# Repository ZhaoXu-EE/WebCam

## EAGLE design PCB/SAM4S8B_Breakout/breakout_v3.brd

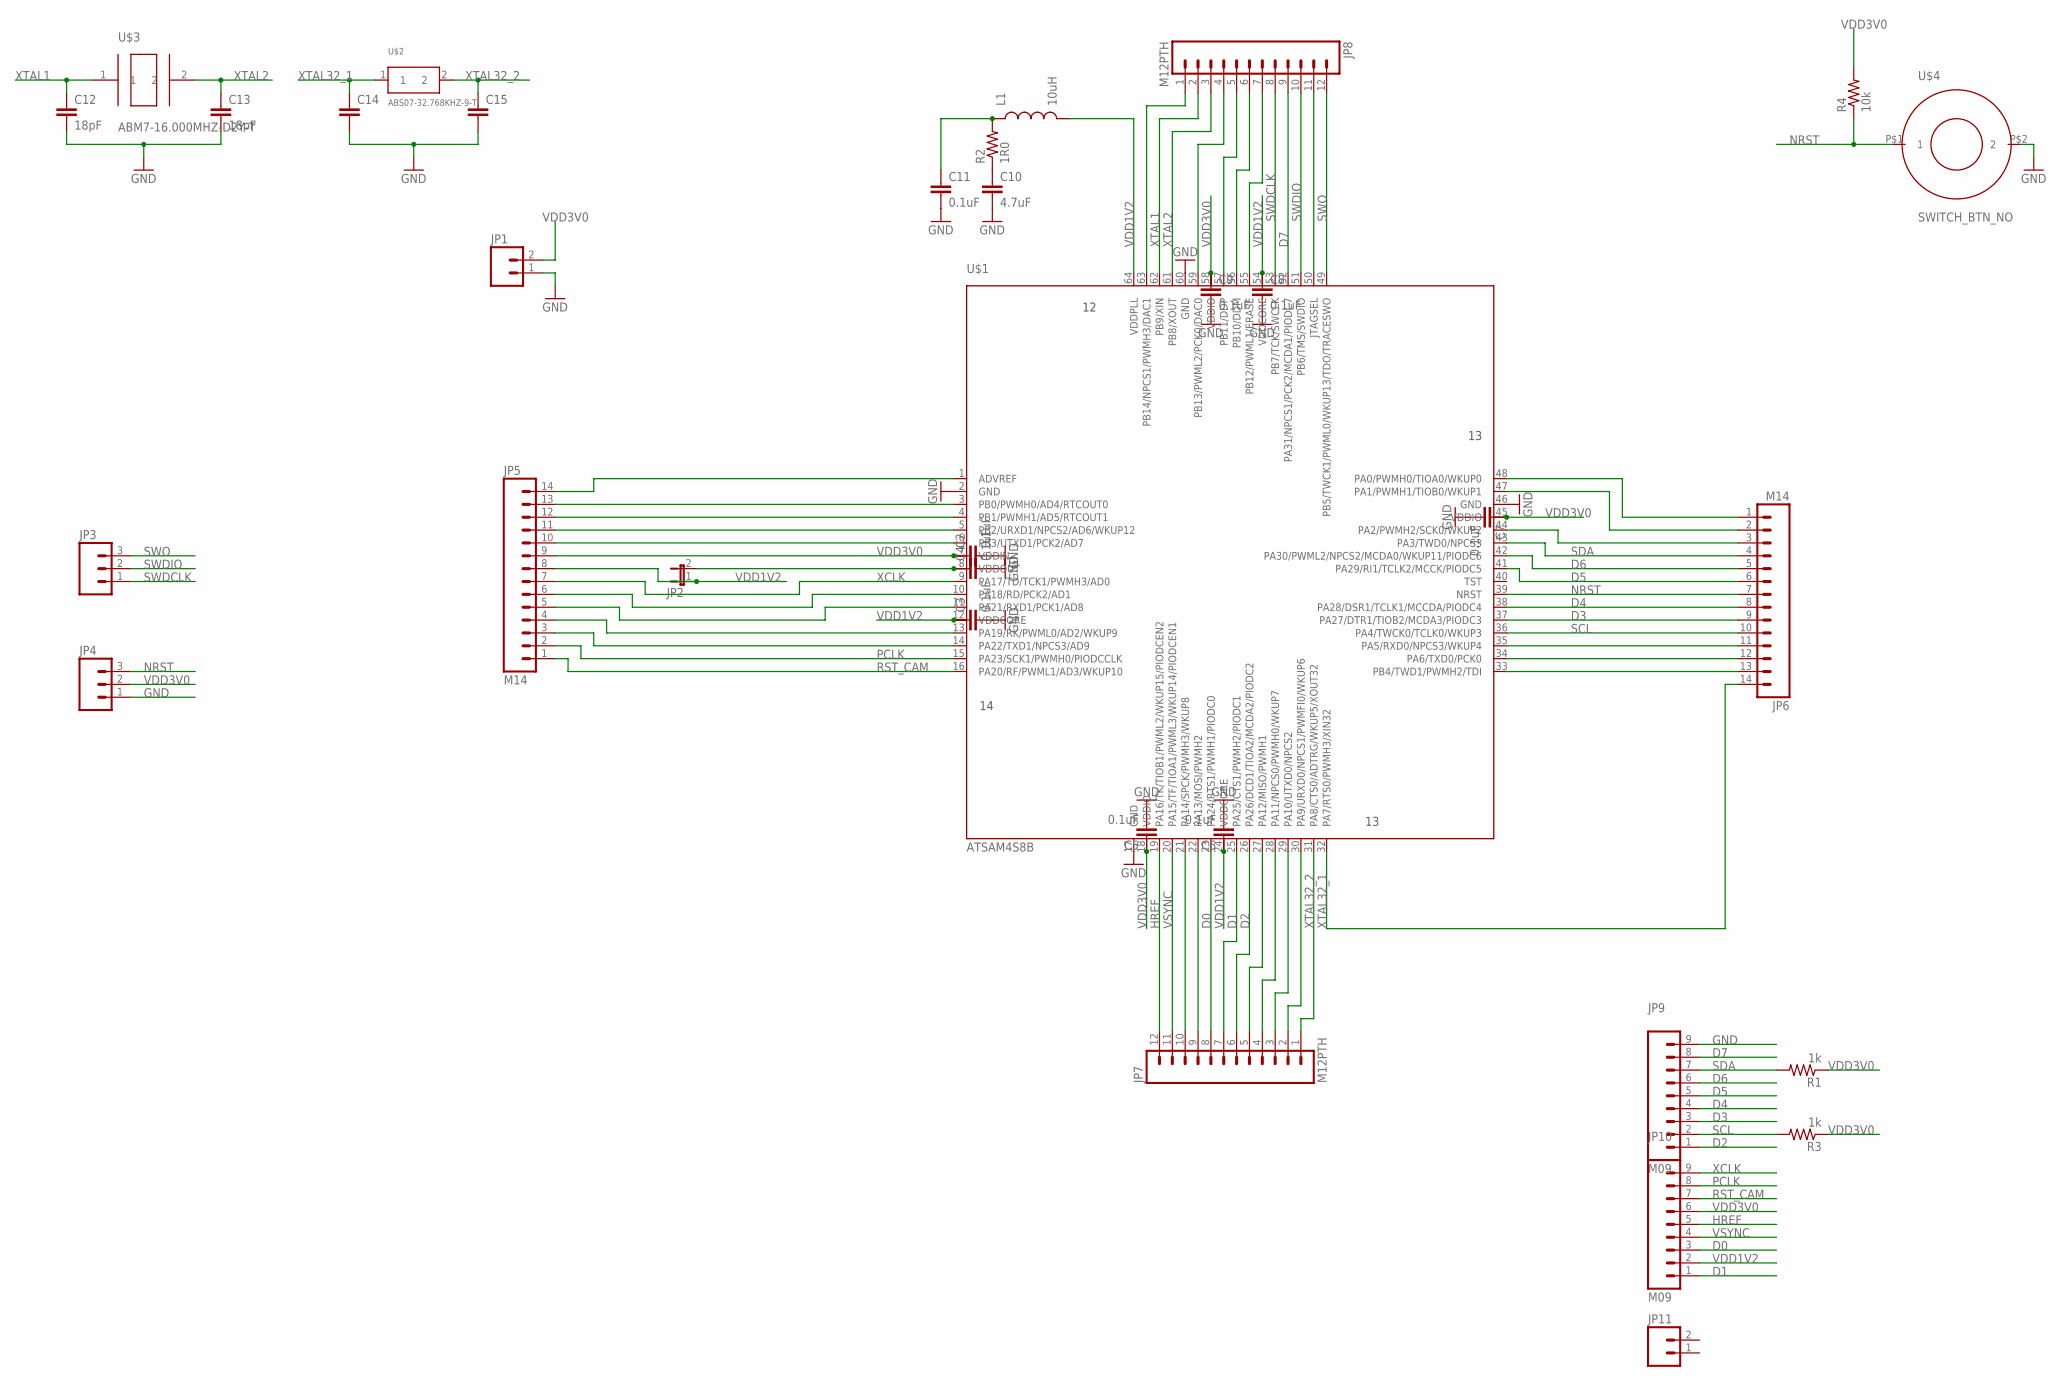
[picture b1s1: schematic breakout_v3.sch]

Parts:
C2, C3, C4, C5, C6, C7, C8, C9, C11: 0.1uF; 0805
C10: 4.7uF; 0805
C12, C13: 18pF; 0805
C14, C15: CAP0805; 0805
JP1, JP11: M02PTH; 1X02
JP2: JUMPER-2PTH; 1X02
JP3, JP4: M03PTH; 1X03
JP5, JP6: M14; 1X14
JP7, JP8: M12PTH; 1X12
JP9, JP10: M09; 1X09
L1: 10uH; 0805
R1, R3: 1k; 0805
R2: 1R0; 0805
R4: 10k; 0805
U$1: ATSAM4S8B; QFP50P1200X1200X160-64N
U$2: ABS07-32.768KHZ-9-T
U$3: ABM7-16.000MHZ-D2Y-T
U$4: SWITCH_BTN_NO; BTN_2

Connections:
D0: JP7.8, JP10.3, U$1.23 (PA24/RTS1/PWMH1/PIODC0)
D1: JP7.7, JP10.1, U$1.25 (PA25/CTS1/PWMH2/PIODC1)
D2: JP7.6, JP9.1, U$1.26 (PA26/DCD1/TIOA2/MCDA2/PIODC2)
D3: JP6.9, JP9.3, U$1.37 (PA27/DTR1/TIOB2/MCDA3/PIODC3)
D4: JP6.8, JP9.4, U$1.38 (PA28/DSR1/TCLK1/MCCDA/PIODC4)
D5: JP6.6, JP9.5, U$1.41 (PA29/RI1/TCLK2/MCCK/PIODC5)
D6: JP6.5, JP9.6, U$1.42 (PA30/PWML2/NPCS2/MCDA0/WKUP11/PIODC6)
D7: JP8.9, JP9.8, U$1.52 (PA31/NPCS1/PCK2/MCDA1/PIODC7)
GND: C2.2, C3.2, C4.2, C5.2, C6.2, C7.2, C8.2, C9.2, C10.2, C11.2, C12.2, C13.2, C14.2, C15.2, JP1.1, JP4.1, JP9.9, U$1.2 (GND), U$1.17 (GND), U$1.46 (GND), U$1.60 (GND), U$4.P$2 (2)
HREF: JP7.12, JP10.5, U$1.19 (PA16/TK/TIOB1/PWML2/WKUP15/PIODCEN2)
unnamed: C4.1, JP2.2, U$1.8 (VDDOUT)
unnamed: C11.1, L1.1, R2.2
unnamed: C10.1, R2.1
unnamed: JP5.14, U$1.1 (ADVREF)
unnamed: JP5.13, U$1.3 (PB0/PWMH0/AD4/RTCOUT0)
unnamed: JP5.12, U$1.4 (PB1/PWMH1/AD5/RTCOUT1)
unnamed: JP5.11, U$1.5 (PB2/URXD1/NPCS2/AD6/WKUP12)
unnamed: JP5.10, U$1.6 (PB3/UTXD1/PCK2/AD7)
unnamed: JP5.6, U$1.10 (PA18/RD/PCK2/AD1)
unnamed: JP5.5, U$1.11 (PA21/RXD1/PCK1/AD8)
unnamed: JP5.4, U$1.13 (PA19/RK/PWML0/AD2/WKUP9)
unnamed: JP5.3, U$1.14 (PA22/TXD1/NPCS3/AD9)
unnamed: JP7.10, U$1.21 (PA14/SPCK/PWMH3/WKUP8)
unnamed: JP7.9, U$1.22 (PA13/MOSI/PWMH2)
unnamed: JP7.5, U$1.27 (PA12/MISO/PWMH1)
unnamed: JP7.4, U$1.28 (PA11/NPCS0/PWMH0/WKUP7)
unnamed: JP7.3, U$1.29 (PA10/UTXD0/NPCS2)
unnamed: JP7.2, U$1.30 (PA9/URXD0/NPCS1/PWMFI0/WKUP6)
unnamed: JP6.13, U$1.33 (PB4/TWD1/PWMH2/TDI)
unnamed: JP6.12, U$1.34 (PA6/TXD0/PCK0)
unnamed: JP6.11, U$1.35 (PA5/RXD0/NPCS3/WKUP4)
unnamed: JP6.3, U$1.44 (PA2/PWMH2/SCK0/WKUP2)
unnamed: JP6.2, U$1.47 (PA1/PWMH1/TIOB0/WKUP1)
unnamed: JP6.1, U$1.48 (PA0/PWMH0/TIOA0/WKUP0)
unnamed: JP8.11, U$1.50 (JTAGSEL)
unnamed: JP8.7, U$1.55 (PB12/PWML1/ERASE)
unnamed: JP8.6, U$1.56 (PB10/DDM)
unnamed: JP8.5, U$1.57 (PB11/DDP)
unnamed: JP8.4, U$1.59 (PB13/PWML2/PCK0/DAC0)
unnamed: JP8.1, U$1.63 (PB14/NPCS1/PWMH3/DAC1)
NRST: JP4.3, JP6.7, R4.1, U$1.39 (NRST), U$4.P$1 (1)
PCLK: JP5.2, JP10.8, U$1.15 (PA23/SCK1/PWMH0/PIODCCLK)
RST_CAM: JP5.1, JP10.7, U$1.16 (PA20/RF/PWML1/AD3/WKUP10)
SCL: JP6.10, JP9.2, R3.2, U$1.36 (PA4/TWCK0/TCLK0/WKUP3)
SDA: JP6.4, JP9.7, R1.2, U$1.43 (PA3/TWD0/NPCS3)
SWDCLK: JP3.1, JP8.8, U$1.53 (PB7/TCK/SWCLK)
SWDIO: JP3.2, JP8.10, U$1.51 (PB6/TMS/SWDIO)
SWO: JP3.3, JP8.12, U$1.49 (PB5/TWCK1/PWML0/WKUP13/TDO/TRACESWO)
VDD1V2: C3.1, C6.1, C8.1, JP2.1, JP5.8, JP10.2, L1.2, U$1.12 (VDDCORE), U$1.24 (VDDCORE), U$1.54 (VDDCORE), U$1.64 (VDDPLL)
VDD3V0: C2.1, C5.1, C7.1, C9.1, JP1.2, JP4.2, JP5.9, JP10.6, R1.1, R3.1, R4.2, U$1.7 (VDDIN), U$1.18 (VDDIO), U$1.45 (VDDIO), U$1.58 (VDDIO)
VSYNC: JP7.11, JP10.4, U$1.20 (PA15/TF/TIOA1/PWML3/WKUP14/PIODCEN1)
XCLK: JP5.7, JP10.9, U$1.9 (PA17/TD/TCK1/PWMH3/AD0)
XTAL1: C12.1, JP8.2, U$1.62 (PB9/XIN), U$3.1
XTAL2: C13.1, JP8.3, U$1.61 (PB8/XOUT), U$3.2
XTAL32_1: C14.1, JP6.14, U$1.32 (PA7/RTS0/PWMH3/XIN32), U$2.1
XTAL32_2: C15.1, JP7.1, U$1.31 (PA8/CTS0/ADTRG/WKUP5/XOUT32), U$2.2

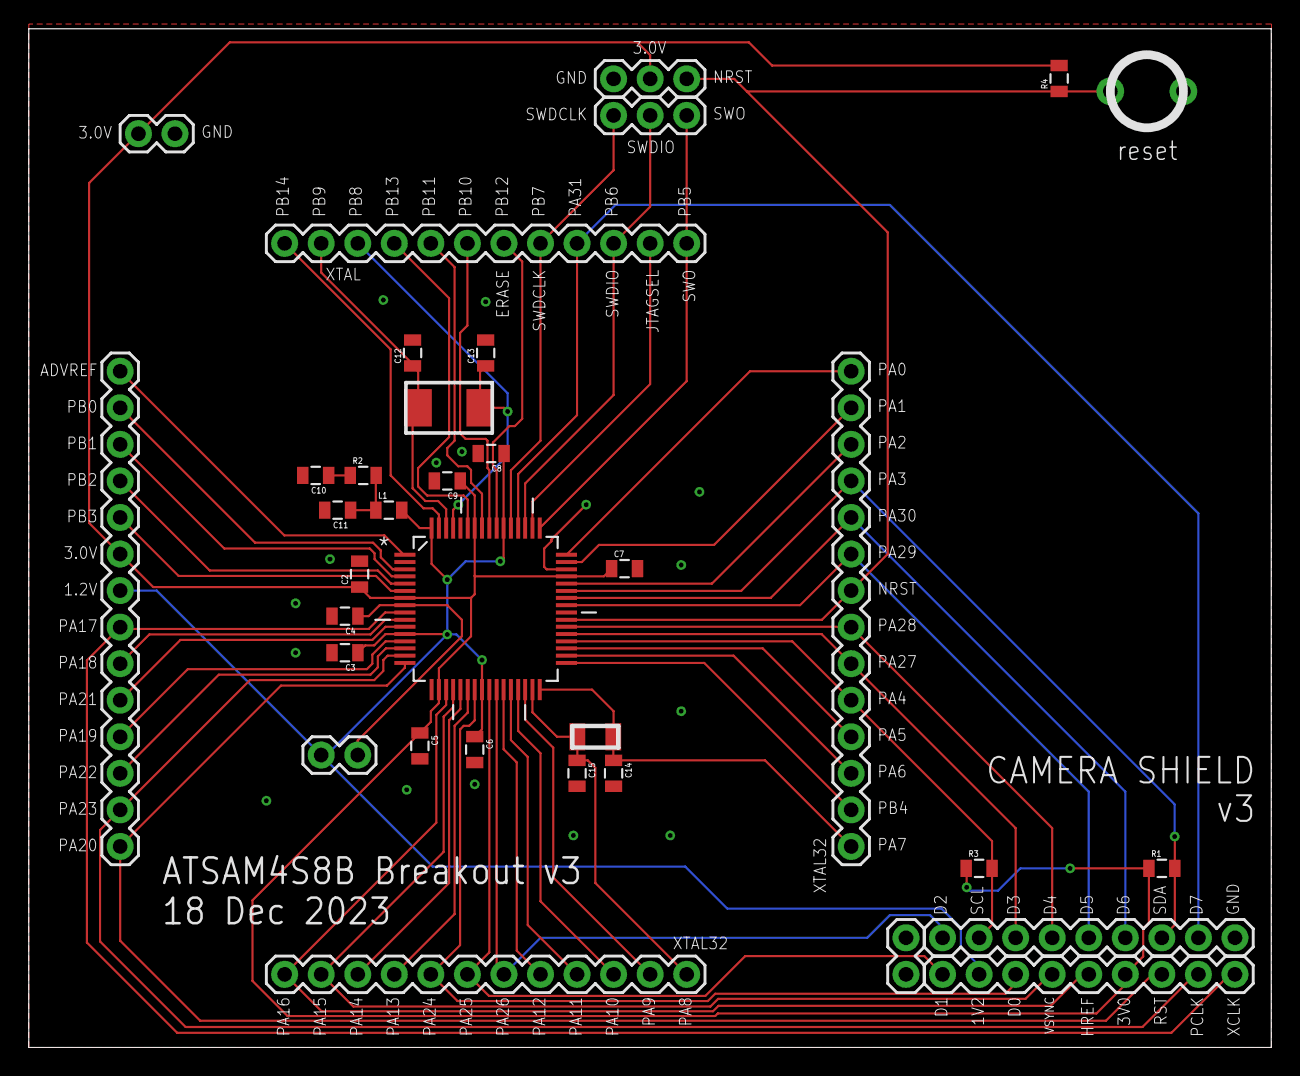
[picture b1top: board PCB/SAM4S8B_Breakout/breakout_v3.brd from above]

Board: 2 copper layers, 86.3 x 70.8 mm, 34 parts (0 on the bottom side), 56 nets.

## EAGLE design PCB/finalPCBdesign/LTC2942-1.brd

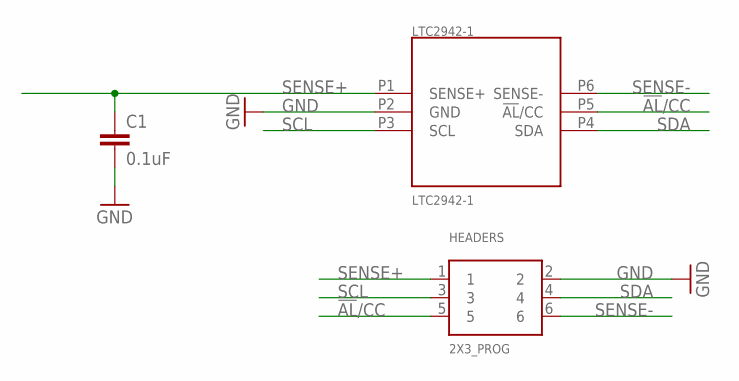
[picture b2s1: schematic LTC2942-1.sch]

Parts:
C1: 0.1uF; 0805
HEADERS: 2X3_PROG; 2X3_0.1IN
LTC2942-1: LTC2942-1

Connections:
!AL!/CC: HEADERS.5, LTC2942-1.P5 (!AL!/CC)
GND: C1.2, HEADERS.2, LTC2942-1.P2 (GND)
SCL: HEADERS.3, LTC2942-1.P3 (SCL)
SDA: HEADERS.4, LTC2942-1.P4 (SDA)
SENSE+: C1.1, HEADERS.1, LTC2942-1.P1 (SENSE+)
SENSE-: HEADERS.6, LTC2942-1.P6 (SENSE-)

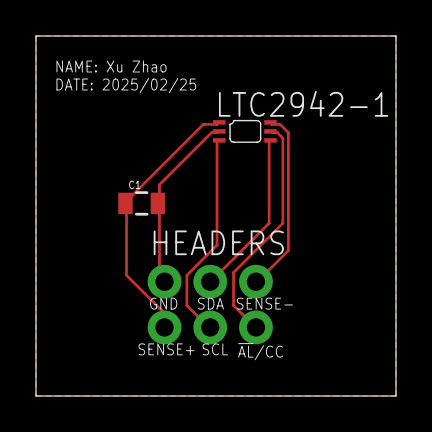
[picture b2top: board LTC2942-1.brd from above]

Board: 2 copper layers, 20.0 x 20.0 mm, 3 parts (0 on the bottom side), 6 nets.

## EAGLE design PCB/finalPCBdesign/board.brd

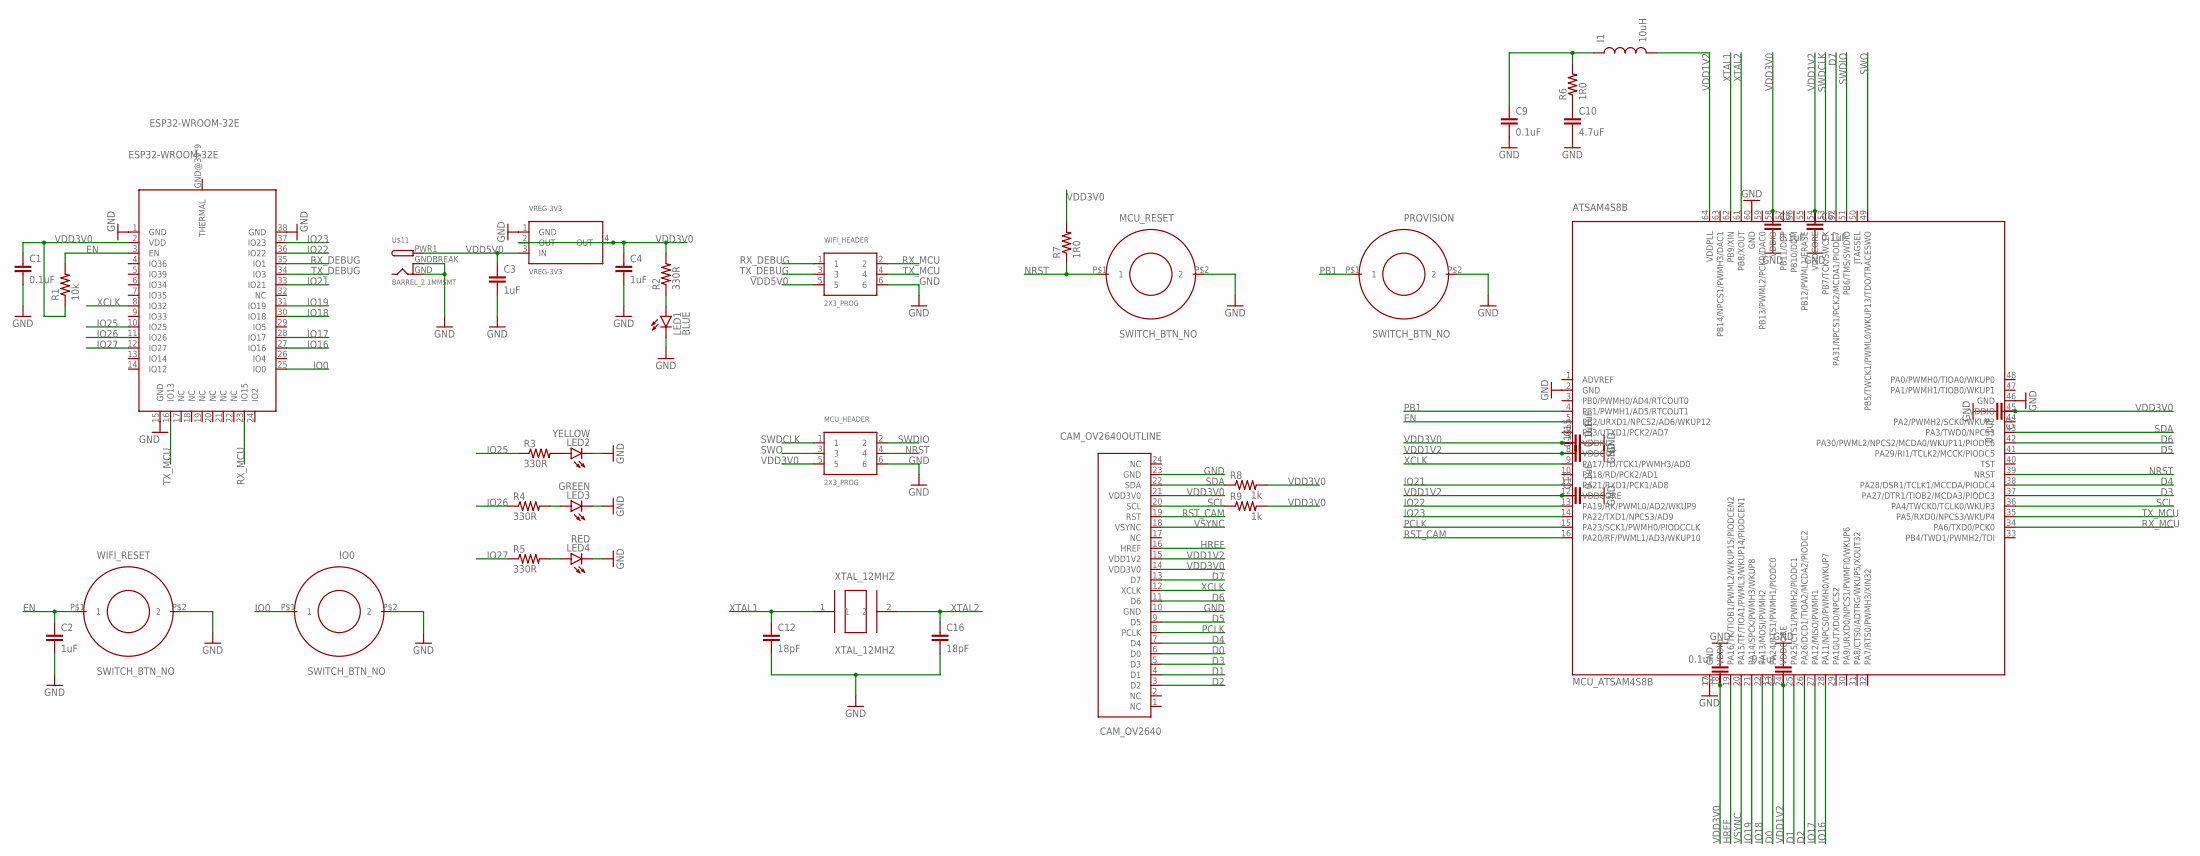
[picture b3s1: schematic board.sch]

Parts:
ATSAM4S8B: MCU_ATSAM4S8B; QFP50P1200X1200X160-64N
C1, C5, C6, C7, C8, C9, C11, C13, C14, C15: 0.1uF; 0805
C2, C3, C4: 1uF; 0805
C10: 4.7uF; 0805
C12, C16: 18pF; 0805
CAM_OV2640: CAM_OV2640OUTLINE; CAM_CONN
ESP32-WROOM-32E: ESP32-WROOM-32E
I1: 10uH; 0805
IO0: SWITCH_BTN_NO; BTN_2
LED1: BLUE; LED-0603
LED2: YELLOW; LED-0603
LED3: GREEN; LED-0603
LED4: RED; LED-0603
MCU_HEADER: 2X3_PROG; 2X3_0.1IN
MCU_RESET: SWITCH_BTN_NO; BTN_2
PROVISION: SWITCH_BTN_NO; BTN_2
R1: 10k; 0805
R2, R3, R4, R5: 330R; 0805
R6, R7: 1R0; 0805
R8, R9: 1k; 0805
U$11: BARREL_2.1MMSMT; DCJACK_2MM_SMT
VREG-3V3: VREG-3V3; R-PDSO-G4_TI
WIFI_HEADER: 2X3_PROG; 2X3_0.1IN
WIFI_RESET: SWITCH_BTN_NO; BTN_2
XTAL_12MHZ: XTAL_12MHZ; ABM7-16.000MHZ-D2Y-T

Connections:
D0: ATSAM4S8B.23 (PA24/RTS1/PWMH1/PIODC0), CAM_OV2640.6 (D0)
D1: ATSAM4S8B.25 (PA25/CTS1/PWMH2/PIODC1), CAM_OV2640.4 (D1)
D2: ATSAM4S8B.26 (PA26/DCD1/TIOA2/MCDA2/PIODC2), CAM_OV2640.3 (D2)
D3: ATSAM4S8B.37 (PA27/DTR1/TIOB2/MCDA3/PIODC3), CAM_OV2640.5 (D3)
D4: ATSAM4S8B.38 (PA28/DSR1/TCLK1/MCCDA/PIODC4), CAM_OV2640.7 (D4)
D5: ATSAM4S8B.41 (PA29/RI1/TCLK2/MCCK/PIODC5), CAM_OV2640.9 (D5)
D6: ATSAM4S8B.42 (PA30/PWML2/NPCS2/MCDA0/WKUP11/PIODC6), CAM_OV2640.11 (D6)
D7: ATSAM4S8B.52 (PA31/NPCS1/PCK2/MCDA1/PIODC7), CAM_OV2640.13 (D7)
EN: ATSAM4S8B.5 (PB2/URXD1/NPCS2/AD6/WKUP12), C2.1, ESP32-WROOM-32E.3 (EN), R1.2, WIFI_RESET.P$1 (1)
GND: ATSAM4S8B.2 (GND), ATSAM4S8B.17 (GND), ATSAM4S8B.46 (GND), ATSAM4S8B.60 (GND), C1.2, C2.2, C3.2, C4.2, C5.2, C6.2, C7.2, C8.2, C9.2, C10.2, C11.2, C12.2, C13.2, C14.2, C15.2, C16.2, CAM_OV2640.10 (GND), CAM_OV2640.23 (GND), ESP32-WROOM-32E.1 (GND), ESP32-WROOM-32E.15 (GND), ESP32-WROOM-32E.38 (GND), IO0.P$2 (2), LED1.C, LED2.C, LED3.C, LED4.C, MCU_HEADER.6, MCU_RESET.P$2 (2), PROVISION.P$2 (2), U$11.GND, U$11.GNDBREAK, VREG-3V3.1 (GND), WIFI_HEADER.6, WIFI_RESET.P$2 (2)
HREF: ATSAM4S8B.19 (PA16/TK/TIOB1/PWML2/WKUP15/PIODCEN2), CAM_OV2640.16 (HREF)
IO0: ESP32-WROOM-32E.25 (IO0), IO0.P$1 (1)
IO16: ATSAM4S8B.28 (PA11/NPCS0/PWMH0/WKUP7), ESP32-WROOM-32E.27 (IO16)
IO17: ATSAM4S8B.27 (PA12/MISO/PWMH1), ESP32-WROOM-32E.28 (IO17)
IO18: ATSAM4S8B.22 (PA13/MOSI/PWMH2), ESP32-WROOM-32E.30 (IO18)
IO19: ATSAM4S8B.21 (PA14/SPCK/PWMH3/WKUP8), ESP32-WROOM-32E.31 (IO19)
IO21: ATSAM4S8B.11 (PA21/RXD1/PCK1/AD8), ESP32-WROOM-32E.33 (IO21)
IO22: ATSAM4S8B.13 (PA19/RK/PWML0/AD2/WKUP9), ESP32-WROOM-32E.36 (IO22)
IO23: ATSAM4S8B.14 (PA22/TXD1/NPCS3/AD9), ESP32-WROOM-32E.37 (IO23)
IO25: ESP32-WROOM-32E.10 (IO25), R3.1
IO26: ESP32-WROOM-32E.11 (IO26), R4.1
IO27: ESP32-WROOM-32E.12 (IO27), R5.1
unnamed: LED1.A, R2.1
unnamed: LED2.A, R3.2
unnamed: LED3.A, R4.2
unnamed: LED4.A, R5.2
unnamed: C10.1, R6.1
unnamed: C9.1, I1.1, R6.2
NRST: ATSAM4S8B.39 (NRST), MCU_HEADER.4, MCU_RESET.P$1 (1), R7.1
PB1: ATSAM4S8B.4 (PB1/PWMH1/AD5/RTCOUT1), PROVISION.P$1 (1)
PCLK: ATSAM4S8B.15 (PA23/SCK1/PWMH0/PIODCCLK), CAM_OV2640.8 (PCLK)
RST_CAM: ATSAM4S8B.16 (PA20/RF/PWML1/AD3/WKUP10), CAM_OV2640.19 (RST)
RX_DEBUG: ESP32-WROOM-32E.35 (IO1), WIFI_HEADER.1
RX_MCU: ATSAM4S8B.34 (PA6/TXD0/PCK0), ESP32-WROOM-32E.23 (IO15), WIFI_HEADER.2
SCL: ATSAM4S8B.36 (PA4/TWCK0/TCLK0/WKUP3), CAM_OV2640.20 (SCL), R9.1
SDA: ATSAM4S8B.43 (PA3/TWD0/NPCS3), CAM_OV2640.22 (SDA), R8.1
SWDCLK: ATSAM4S8B.53 (PB7/TCK/SWCLK), MCU_HEADER.1
SWDIO: ATSAM4S8B.51 (PB6/TMS/SWDIO), MCU_HEADER.2
SWO: ATSAM4S8B.49 (PB5/TWCK1/PWML0/WKUP13/TDO/TRACESWO), MCU_HEADER.3
TX_DEBUG: ESP32-WROOM-32E.34 (IO3), WIFI_HEADER.3
TX_MCU: ATSAM4S8B.35 (PA5/RXD0/NPCS3/WKUP4), ESP32-WROOM-32E.16 (IO13), WIFI_HEADER.4
VDD1V2: ATSAM4S8B.8 (VDDOUT), ATSAM4S8B.12 (VDDCORE), ATSAM4S8B.24 (VDDCORE), ATSAM4S8B.54 (VDDCORE), ATSAM4S8B.64 (VDDPLL), C6.1, C11.1, C13.1, C14.1, CAM_OV2640.15 (VDD1V2), I1.2
VDD3V0: ATSAM4S8B.7 (VDDIN), ATSAM4S8B.18 (VDDIO), ATSAM4S8B.45 (VDDIO), ATSAM4S8B.58 (VDDIO), C1.1, C4.1, C5.1, C7.1, C8.1, C15.1, CAM_OV2640.14 (VDD3V0), CAM_OV2640.21 (VDD3V0), ESP32-WROOM-32E.2 (VDD), MCU_HEADER.5, R1.1, R2.2, R7.2, R8.2, R9.2, VREG-3V3.2 (OUT), VREG-3V3.4 (OUT)
VDD5V0: C3.1, U$11.PWR1 (PWR), VREG-3V3.3 (IN), WIFI_HEADER.5
VSYNC: ATSAM4S8B.20 (PA15/TF/TIOA1/PWML3/WKUP14/PIODCEN1), CAM_OV2640.18 (VSYNC)
XCLK: ATSAM4S8B.9 (PA17/TD/TCK1/PWMH3/AD0), CAM_OV2640.12 (XCLK), ESP32-WROOM-32E.8 (IO32)
XTAL1: ATSAM4S8B.62 (PB9/XIN), C12.1, XTAL_12MHZ.1
XTAL2: ATSAM4S8B.61 (PB8/XOUT), C16.1, XTAL_12MHZ.2

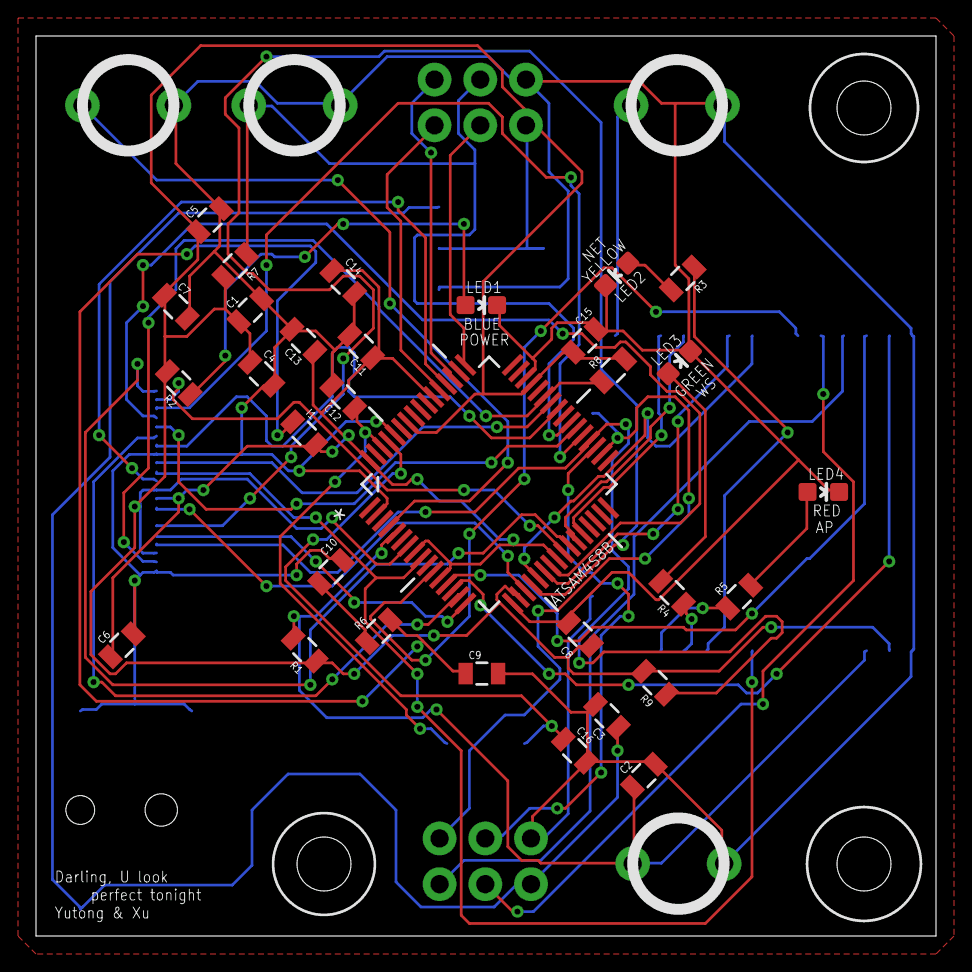
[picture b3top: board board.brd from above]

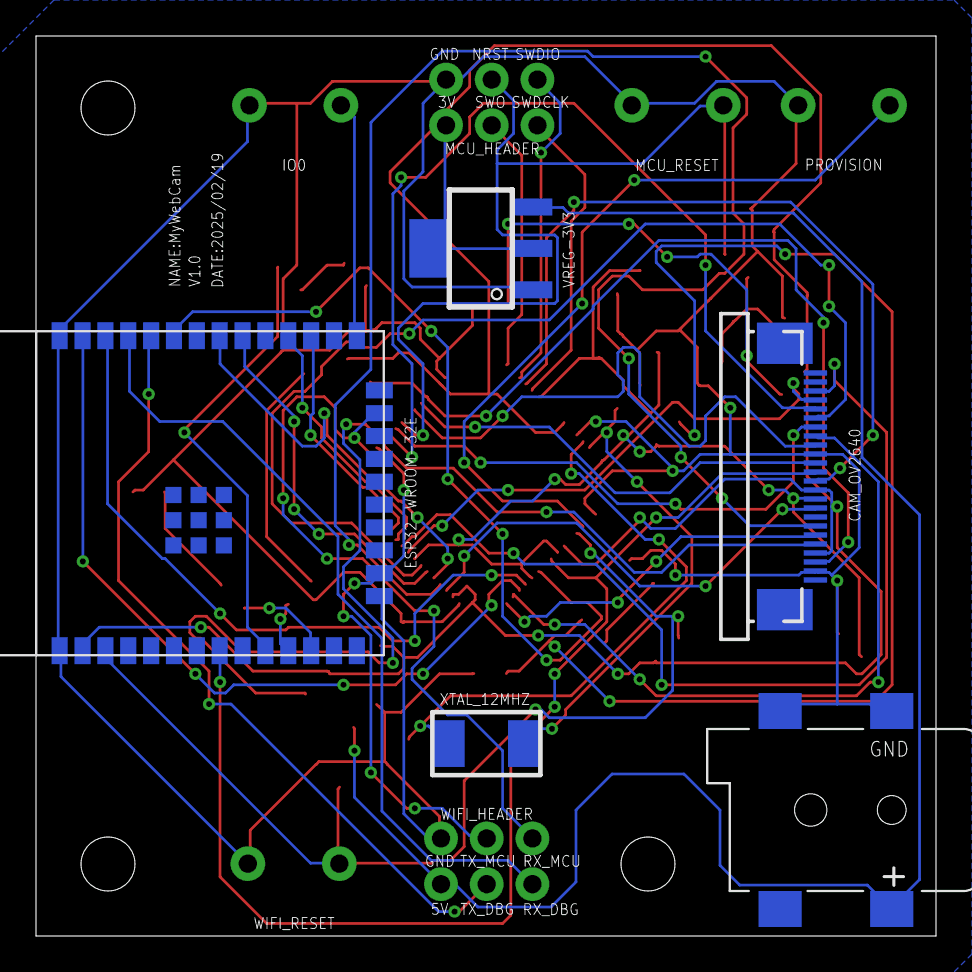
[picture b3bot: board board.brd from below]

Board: 2 copper layers, 50.0 x 50.0 mm, 42 parts (5 on the bottom side), 48 nets.

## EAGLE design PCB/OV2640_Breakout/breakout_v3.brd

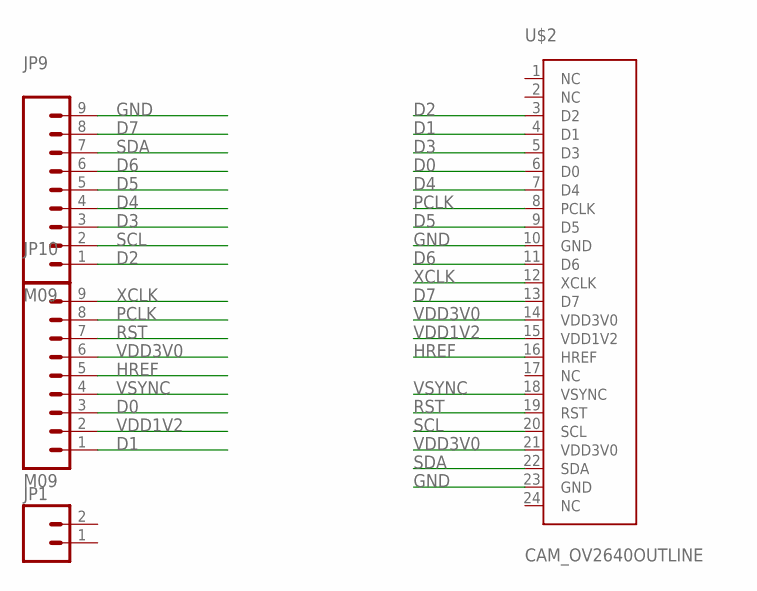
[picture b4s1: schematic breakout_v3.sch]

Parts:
JP1: M02PTH; 1X02
JP9, JP10: M09; 1X09
U$2: CAM_OV2640OUTLINE; CAM_CONN

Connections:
D0: JP10.3, U$2.6 (D0)
D1: JP10.1, U$2.4 (D1)
D2: JP9.1, U$2.3 (D2)
D3: JP9.3, U$2.5 (D3)
D4: JP9.4, U$2.7 (D4)
D5: JP9.5, U$2.9 (D5)
D6: JP9.6, U$2.11 (D6)
D7: JP9.8, U$2.13 (D7)
GND: JP9.9, U$2.10 (GND), U$2.23 (GND)
HREF: JP10.5, U$2.16 (HREF)
PCLK: JP10.8, U$2.8 (PCLK)
RST: JP10.7, U$2.19 (RST)
SCL: JP9.2, U$2.20 (SCL)
SDA: JP9.7, U$2.22 (SDA)
VDD1V2: JP10.2, U$2.15 (VDD1V2)
VDD3V0: JP10.6, U$2.14 (VDD3V0), U$2.21 (VDD3V0)
VSYNC: JP10.4, U$2.18 (VSYNC)
XCLK: JP10.9, U$2.12 (XCLK)

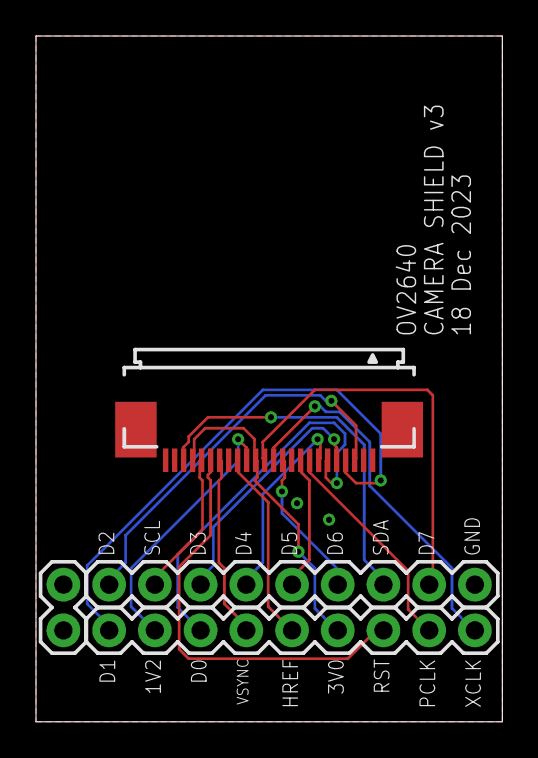
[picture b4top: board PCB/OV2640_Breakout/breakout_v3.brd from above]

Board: 2 copper layers, 25.9 x 38.1 mm, 4 parts (0 on the bottom side), 18 nets.

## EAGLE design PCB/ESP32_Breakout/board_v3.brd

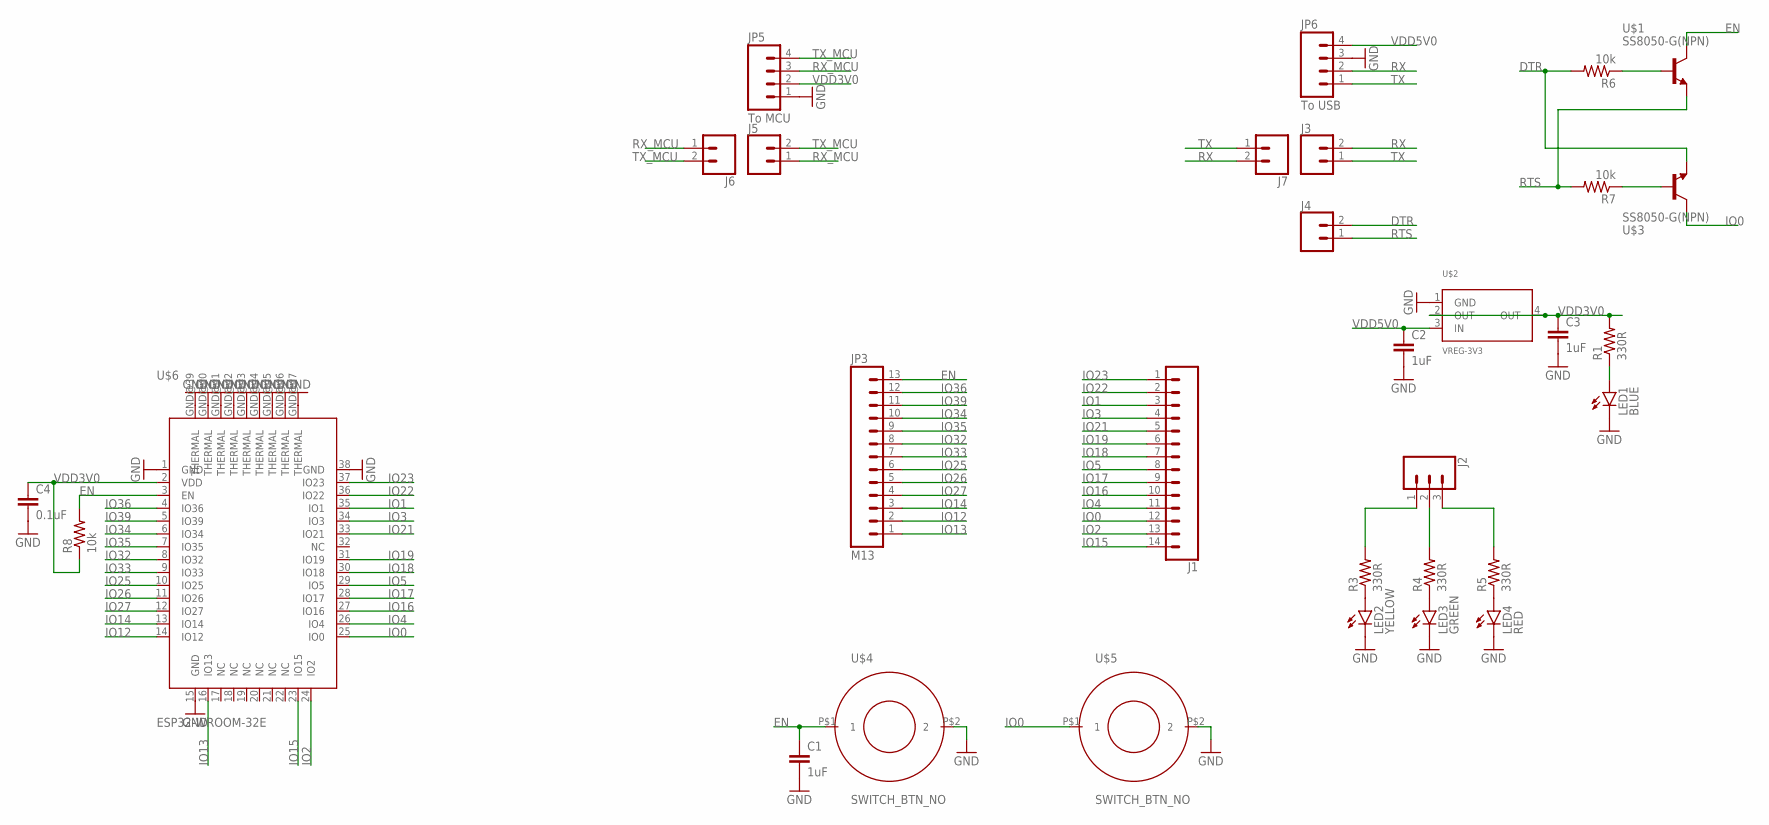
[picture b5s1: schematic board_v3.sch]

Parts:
C1, C2, C3: 1uF; 0805
C4: 0.1uF; 0805
J1: CONN_14; 1X14
J2: CONN_03; 1X03
J3, J4, J5, J6, J7: CONN_02; 1X02
JP3: M13; 1X13
JP5: To MCU; 1X04
JP6: To USB; 1X04
LED1: BLUE; LED-0603
LED2: YELLOW; LED-0603
LED3: GREEN; LED-0603
LED4: RED; LED-0603
R1, R3, R4, R5: 330R; 0805
R6, R7, R8: 10k; 0805
U$1, U$3: SS8050-G(NPN); SOT-23(SS8050-G)
U$2: VREG-3V3; R-PDSO-G4_TI
U$4, U$5: SWITCH_BTN_NO; BTN_2
U$6: ESP32-WROOM-32E

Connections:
DTR: J4.2, R6.2, U$3.2 (E)
EN: C1.1, JP3.13, R8.2, U$1.3 (C), U$4.P$1 (1), U$6.3 (EN)
GND: C1.2, C2.2, C3.2, C4.2, JP5.1, JP6.3, LED1.C, LED2.C, LED3.C, LED4.C, U$2.1 (GND), U$4.P$2 (2), U$5.P$2 (2), U$6.1 (GND), U$6.15 (GND), U$6.38 (GND), U$6.GND@39 (THERMAL), U$6.GND@40 (THERMAL), U$6.GND@41 (THERMAL), U$6.GND@42 (THERMAL), U$6.GND@43 (THERMAL), U$6.GND@44 (THERMAL), U$6.GND@45 (THERMAL), U$6.GND@46 (THERMAL), U$6.GND@47 (THERMAL)
IO0: J1.12, U$3.3 (C), U$5.P$1 (1), U$6.25 (IO0)
IO1: J1.3, U$6.35 (IO1)
IO2: J1.13, U$6.24 (IO2)
IO3: J1.4, U$6.34 (IO3)
IO4: J1.11, U$6.26 (IO4)
IO5: J1.8, U$6.29 (IO5)
IO12: JP3.2, U$6.14 (IO12)
IO13: JP3.1, U$6.16 (IO13)
IO14: JP3.3, U$6.13 (IO14)
IO15: J1.14, U$6.23 (IO15)
IO16: J1.10, U$6.27 (IO16)
IO17: J1.9, U$6.28 (IO17)
IO18: J1.7, U$6.30 (IO18)
IO19: J1.6, U$6.31 (IO19)
IO21: J1.5, U$6.33 (IO21)
IO22: J1.2, U$6.36 (IO22)
IO23: J1.1, U$6.37 (IO23)
IO25: JP3.6, U$6.10 (IO25)
IO26: JP3.5, U$6.11 (IO26)
IO27: JP3.4, U$6.12 (IO27)
IO32: JP3.8, U$6.8 (IO32)
IO33: JP3.7, U$6.9 (IO33)
IO34: JP3.10, U$6.6 (IO34)
IO35: JP3.9, U$6.7 (IO35)
IO36: JP3.12, U$6.4 (IO36)
IO39: JP3.11, U$6.5 (IO39)
unnamed: LED1.A, R1.1
unnamed: J2.1, R3.2
unnamed: J2.3, R5.2
unnamed: J2.2, R4.2
unnamed: R6.1, U$1.1 (B)
unnamed: R7.1, U$3.1 (B)
unnamed: LED2.A, R3.1
unnamed: LED3.A, R4.1
unnamed: LED4.A, R5.1
RTS: J4.1, R7.2, U$1.2 (E)
RX: J3.2, J7.2, JP6.2
RX_MCU: J5.1, J6.1, JP5.3
TX: J3.1, J7.1, JP6.1
TX_MCU: J5.2, J6.2, JP5.4
VDD3V0: C3.1, C4.1, JP5.2, R1.2, R8.1, U$2.2 (OUT), U$2.4 (OUT), U$6.2 (VDD)
VDD5V0: C2.1, JP6.4, U$2.3 (IN)

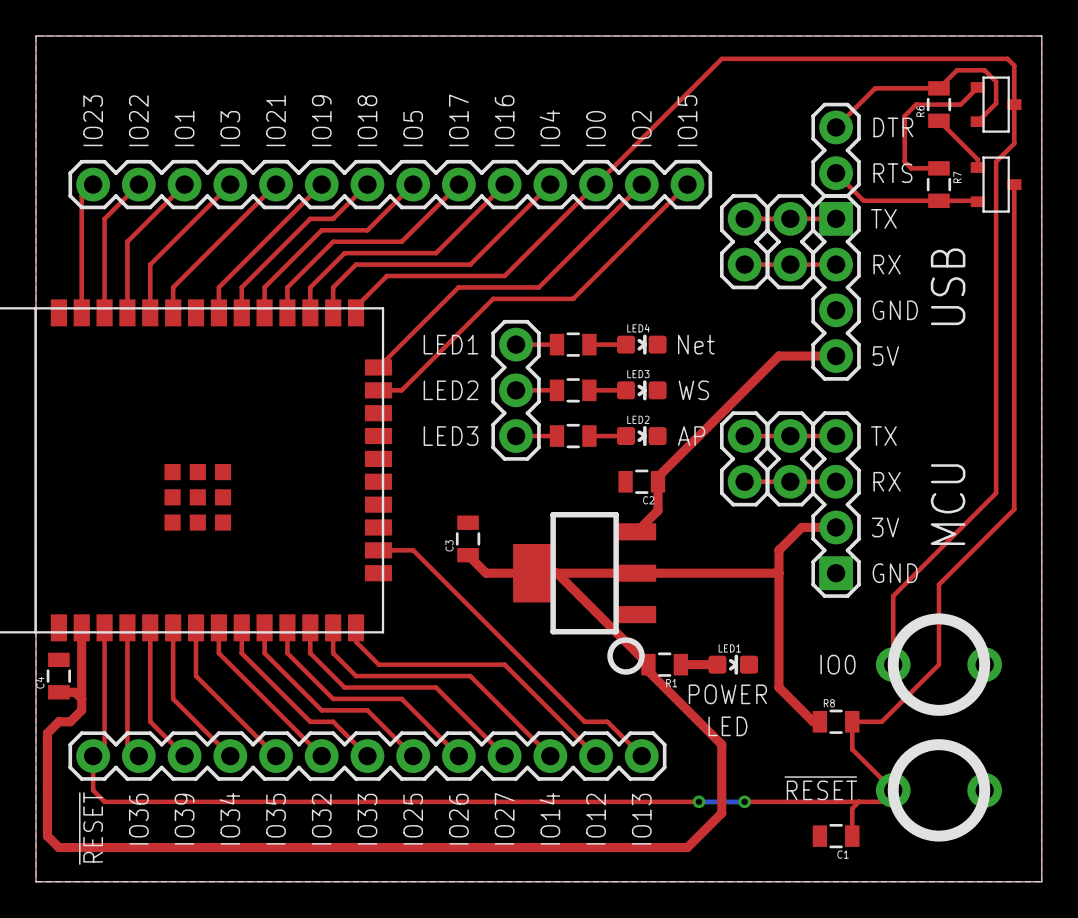
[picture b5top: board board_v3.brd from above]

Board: 2 copper layers, 55.9 x 47.0 mm, 31 parts (0 on the bottom side), 45 nets.

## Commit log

2025-04-03 commit cad
2025-04-03 commit pcb
2025-04-03 commit firmware
2025-04-03 commit website
2025-04-03 commit datasheet
2025-04-03 commit document

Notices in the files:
parts and their libraries:
SparkFun: Licensing: CC v3.0 Share-Alike You are welcome to use this library for commercial purposes.
SparkFun-Connectors: Licensing: Creative Commons ShareAlike 4.0 International - https://creativecommons.org/licenses/by-sa/4.0
